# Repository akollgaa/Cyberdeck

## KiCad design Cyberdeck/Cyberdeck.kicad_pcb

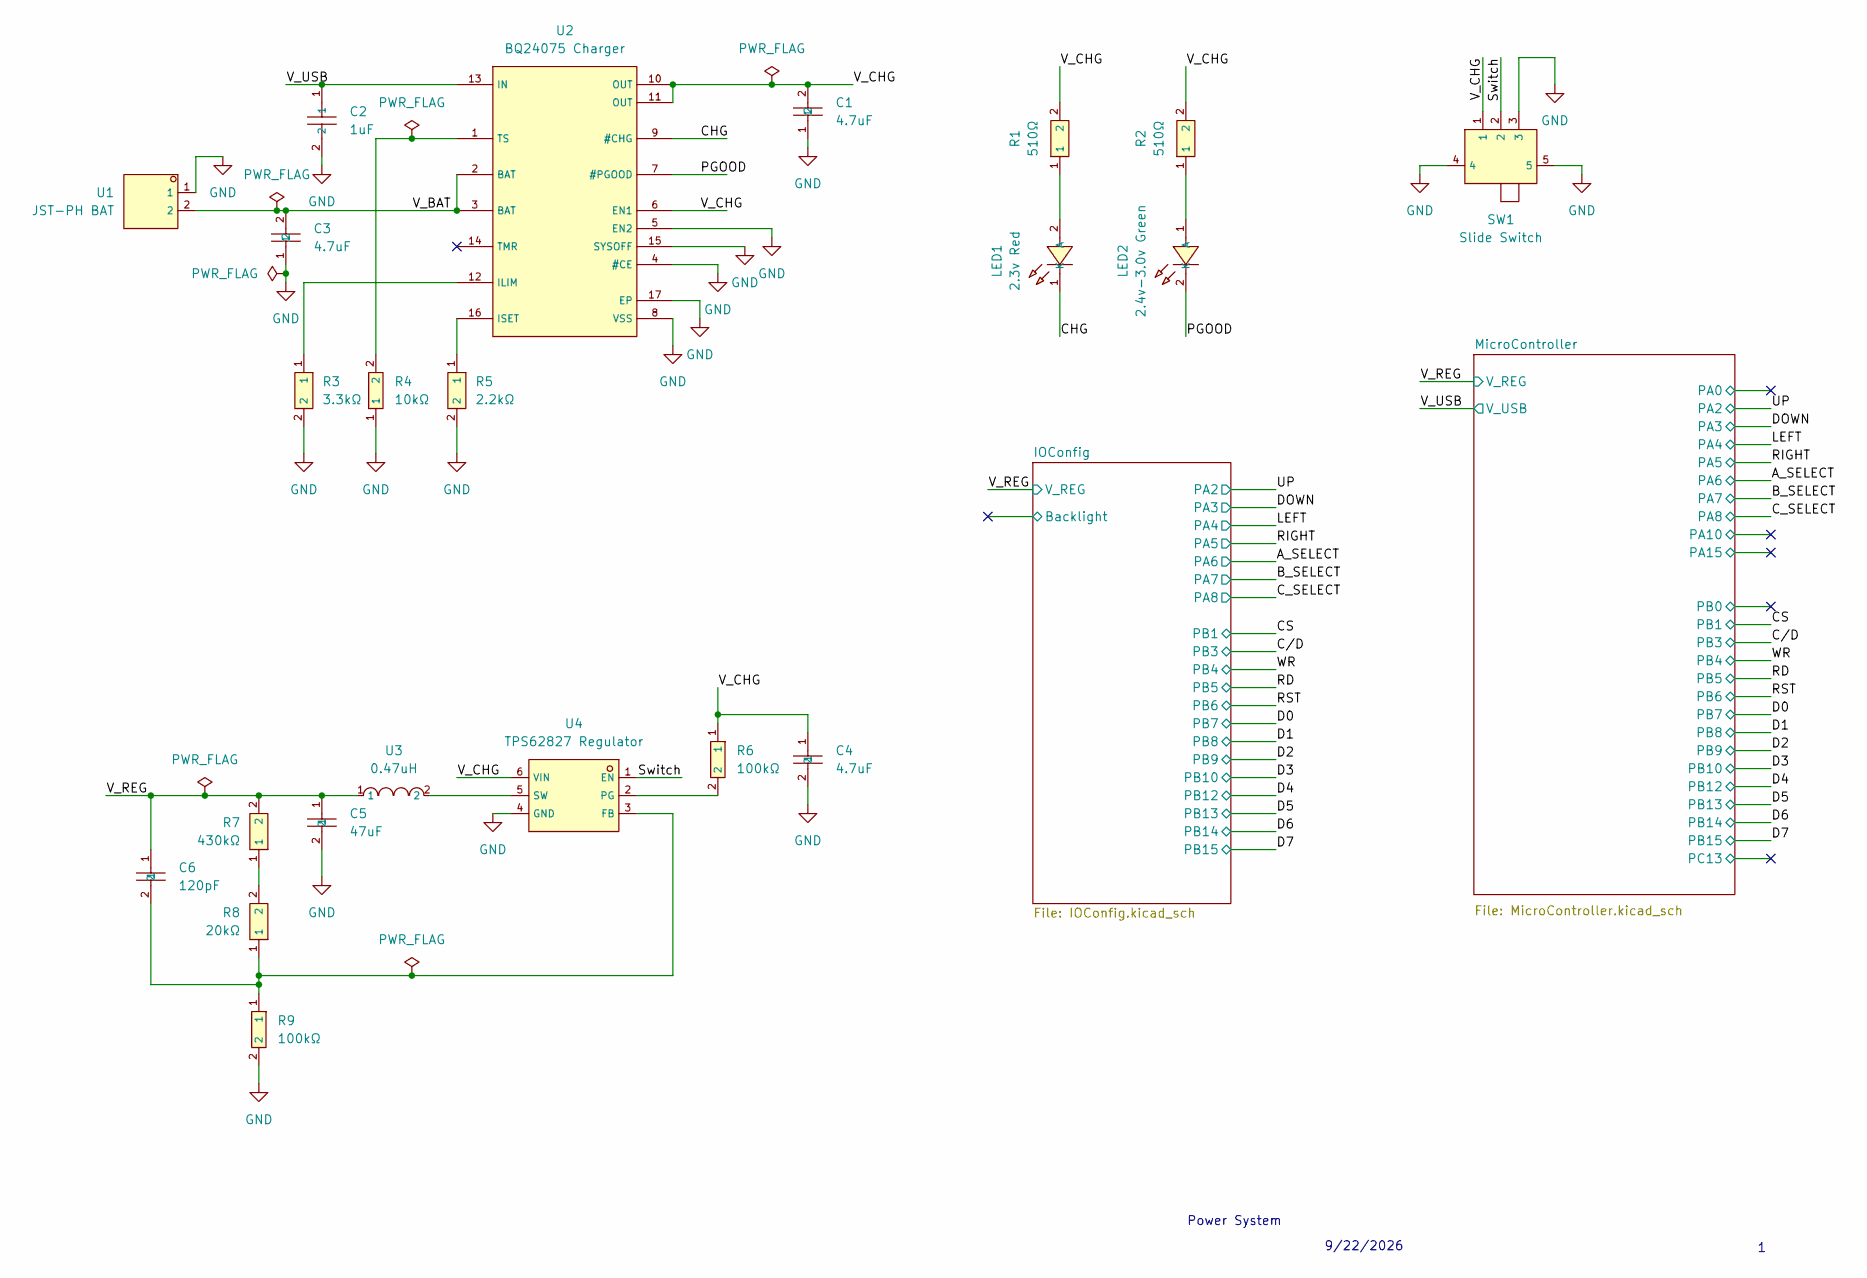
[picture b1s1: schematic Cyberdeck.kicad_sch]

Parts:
C1, C3, C4: 4.7uF; C69335_C0603; LCSC C69335
C2: 1uF; C5199872_C0603; LCSC C5199872
C5: 47uF; C140782_C0603; LCSC C140782
C6: 120pF; C107035_C0603; LCSC C107035
LED1: 2.3v Red; C965799_LED0603-RD_RED; LCSC C965799
LED2: 2.4v-3.0v Green; C19171301_LED0603-FD; LCSC C19171301
R1, R2: 510Ω; C2907048_R0603; LCSC C2907048
R3: 3.3kΩ; C2907023_R0603; LCSC C2907023
R4: 10kΩ; C98220_R0603; LCSC C98220
R5: 2.2kΩ; C2907005_R0603; LCSC C2907005
R6, R9: 100kΩ; C14675_R0603; LCSC C14675
R7: 430kΩ; C2907036_R0603; LCSC C2907036
R8: 20kΩ; C2907011_R0603; LCSC C2907011
SW1: Slide Switch; C2939726_SW-TH_SS12D07VG4; LCSC C2939726
U1: JST-PH BAT; C173752_CONN-TH_S2B-PH-K-S-LF-SN; LCSC C173752
U2: BQ24075 Charger; C15464_QFN-16_L3_0-W3_0-P0_50-TL-EP1_7; LCSC C15464
U3: 0.47uH; C269773_L0806; LCSC C269773
U4: TPS62827 Regulator; C2071448_VSON-6_L1_5-W1_5-P0_50-TL; LCSC C2071448

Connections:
/CHG: LED1.1 (K), U2.9 (#CHG)
/PGOOD: LED2.2 (K), U2.7 (#PGOOD)
/Switch: SW1.2, U4.1 (EN)
/V_BAT: C3.2, U1.2, U2.2 (BAT), U2.3 (BAT)
/V_CHG: C1.2, C4.1, R1.2, R2.2, R6.1, SW1.1, U2.6 (EN1), U2.10 (OUT), U2.11 (OUT), U4.6 (VIN)
/V_REG: C5.1, C6.1, R7.2, U3.1; also elsewhere on the board
/V_USB: C2.1, U2.13 (IN); also elsewhere on the board
GND: C1.1, C2.2, C3.1, C4.2, C5.2, R3.2, R4.1, R5.2, R9.2, SW1.3, SW1.4, SW1.5, U1.1, U2.4 (#CE), U2.5 (EN2), U2.8 (VSS), U2.15 (SYSOFF), U2.17 (EP), U4.4 (GND); also elsewhere on the board
unnamed: LED1.2 (A), R1.1
unnamed: LED2.1 (A), R2.1
unnamed: R7.1, R8.2
unnamed: R3.1, U2.12 (ILIM)
unnamed: R5.1, U2.16 (ISET)
unnamed: R4.2, U2.1 (TS)
unnamed: C6.2, R8.1, R9.1, U4.3 (FB)
unnamed: R6.2, U4.2 (PG)
unnamed: U3.2, U4.5 (SW)

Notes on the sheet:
9/22/2026
Power System

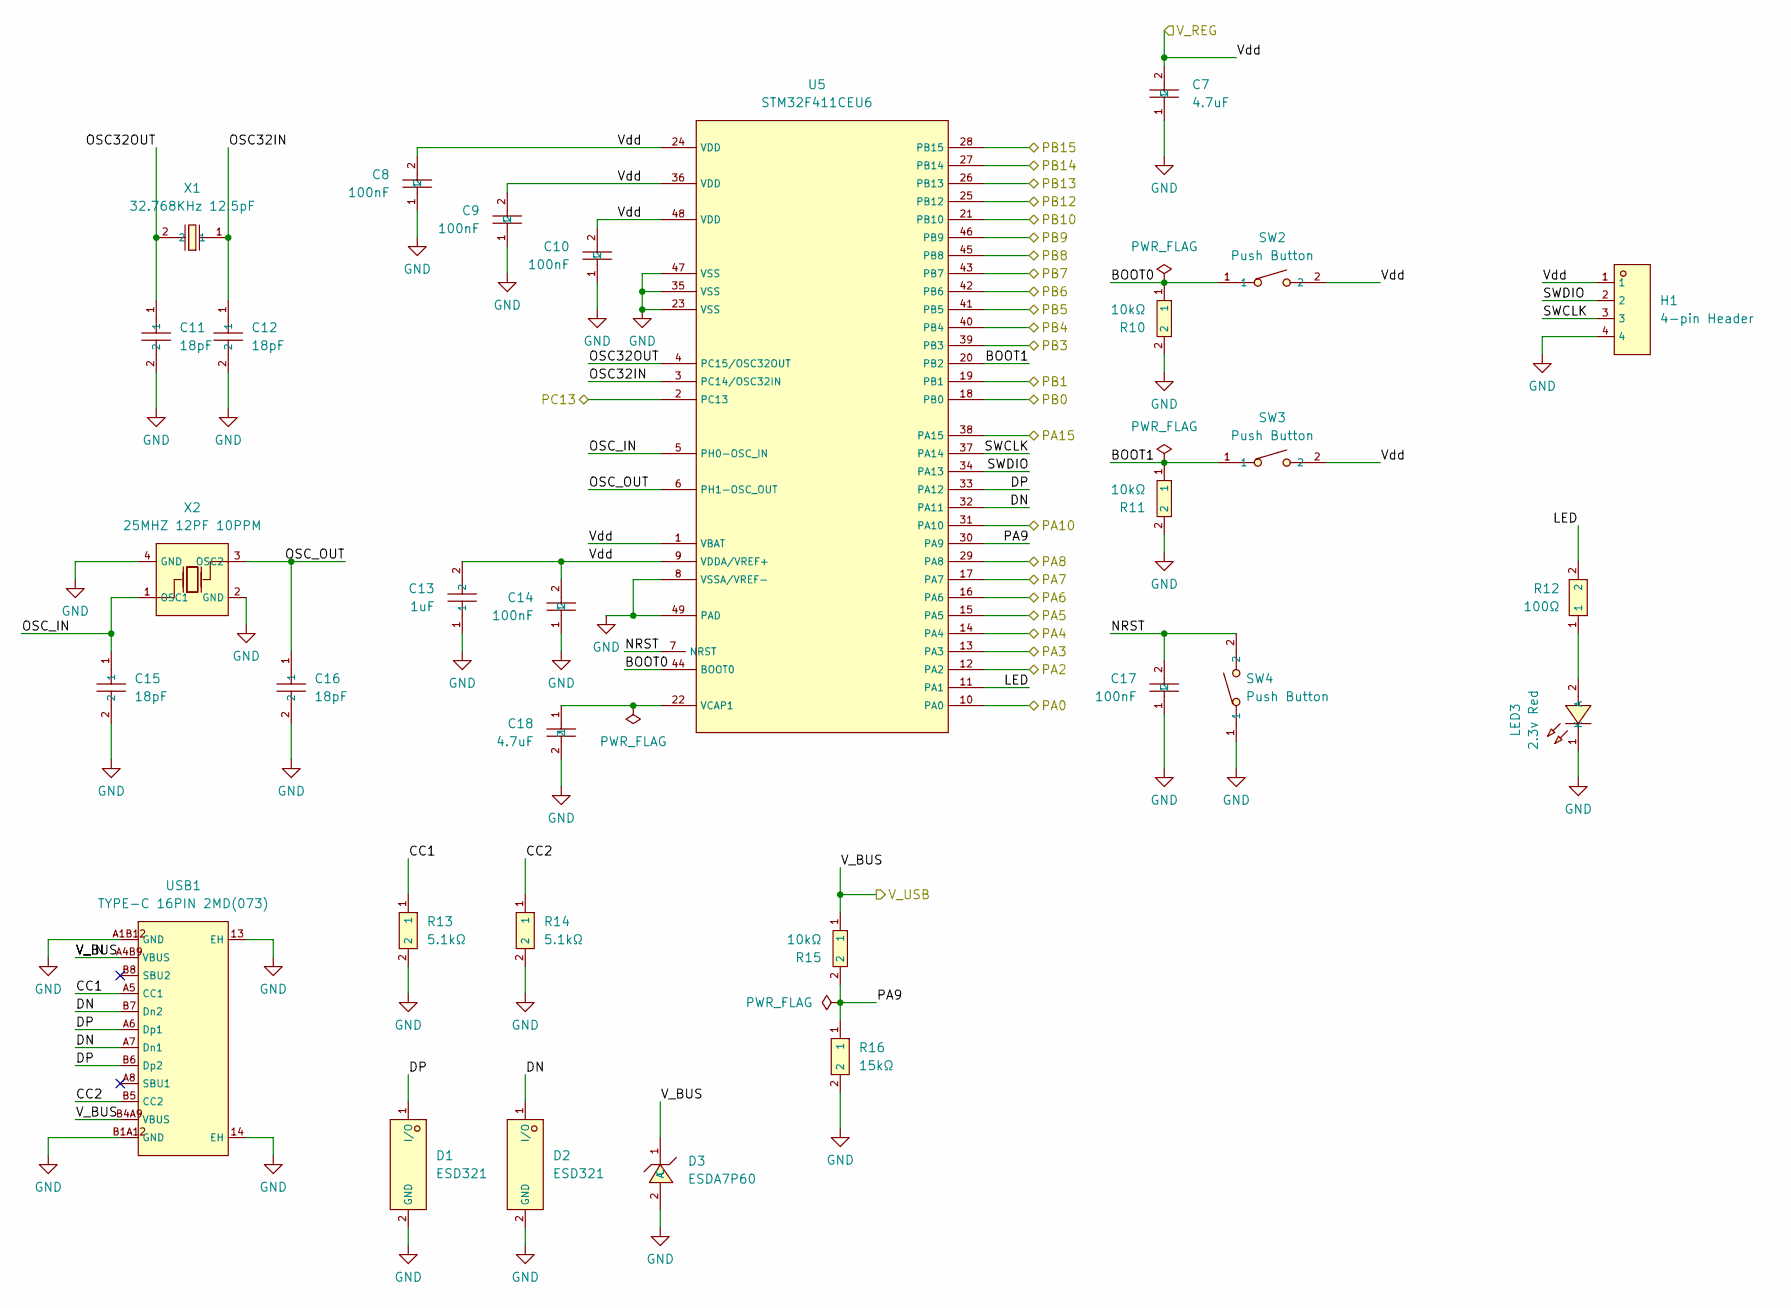
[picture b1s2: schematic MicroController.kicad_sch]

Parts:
C7, C18: 4.7uF; C69335_C0603; LCSC C69335
C8, C9, C10, C14, C17: 100nF; C66501_C0603; LCSC C66501
C11, C12, C15, C16: 18pF; C541431_C0402; LCSC C541431
C13: 1uF; C5199872_C0603; LCSC C5199872
D1, D2: ESD321; C2868952_X1SON-2_L1_0-W0_6-P0_65-RD-1; LCSC C2868952
D3: ESDA7P60; C1975146_D1610-RD; LCSC C1975146
H1: 4-pin Header; C2691448_HDR-TH_4P-P2_54-V-M; LCSC C2691448
LED3: 2.3v Red; C965799_LED0603-RD_RED; LCSC C965799
R10, R11, R15: 10kΩ; C98220_R0603; LCSC C98220
R12: 100Ω; C2906981_R0603; LCSC C2906981
R13, R14: 5.1kΩ; C2907044_R0603; LCSC C2907044
R16: 15kΩ; C2906995_R0603; LCSC C2906995
SW2, SW3, SW4: Push Button; C720477_SW-SMD_L3_9-W3_0-P4_45; LCSC C720477
U5: STM32F411CEU6; C60420_UFQFPN-48_L7_0-W7_0-P0_50-BL-EP; LCSC C60420
USB1: TYPE-C 16PIN 2MD(073); C2765186_USB-C-SMD_TYPE-C-16PIN-2MD-073; LCSC C2765186
X1: 32.768KHz 12.5pF; C32346_FC-135R_L3_2-W1_5; LCSC C32346
X2: 25MHZ 12PF 10PPM; C9006_CRYSTAL-SMD_4P-L3_2-W2_5-BL; LCSC C9006

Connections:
/A_SELECT: U5.16 (PA6); also elsewhere on the board
/B_SELECT: U5.17 (PA7); also elsewhere on the board
/CS: U5.19 (PB1); also elsewhere on the board
/C_SELECT: U5.29 (PA8); also elsewhere on the board
/C/D: U5.39 (PB3); also elsewhere on the board
/D0: U5.43 (PB7); also elsewhere on the board
/D1: U5.45 (PB8); also elsewhere on the board
/D2: U5.46 (PB9); also elsewhere on the board
/D3: U5.21 (PB10); also elsewhere on the board
/D4: U5.25 (PB12); also elsewhere on the board
/D5: U5.26 (PB13); also elsewhere on the board
/D6: U5.27 (PB14); also elsewhere on the board
/D7: U5.28 (PB15); also elsewhere on the board
/DOWN: U5.13 (PA3); also elsewhere on the board
/LEFT: U5.14 (PA4); also elsewhere on the board
/MicroController/BOOT0: R10.1, SW2.1, U5.44 (BOOT0)
/MicroController/BOOT1: R11.1, SW3.1, U5.20 (PB2)
/MicroController/CC1: R13.1, USB1.A5 (CC1)
/MicroController/CC2: R14.1, USB1.B5 (CC2)
/MicroController/DN: D2.1 (I/O), U5.32 (PA11), USB1.A7 (Dn1), USB1.B7 (Dn2)
/MicroController/DP: D1.1 (I/O), U5.33 (PA12), USB1.A6 (Dp1), USB1.B6 (Dp2)
/MicroController/LED: R12.2, U5.11 (PA1)
/MicroController/NRST: C17.2, SW4.2, U5.7 (NRST)
/MicroController/OSC32IN: C12.1, U5.3 (PC14/OSC32IN), X1.1
/MicroController/OSC32OUT: C11.1, U5.4 (PC15/OSC32OUT), X1.2
/MicroController/OSC_IN: C15.1, U5.5 (PH0-OSC_IN), X2.1 (OSC1)
/MicroController/OSC_OUT: C16.1, U5.6 (PH1-OSC_OUT), X2.3 (OSC2)
/MicroController/PA0: U5.10 (PA0); also elsewhere on the board
/MicroController/PA9: R15.2, R16.1, U5.30 (PA9)
/MicroController/PA10: U5.31 (PA10); also elsewhere on the board
/MicroController/PA15: U5.38 (PA15); also elsewhere on the board
/MicroController/PB0: U5.18 (PB0); also elsewhere on the board
/MicroController/PC13: U5.2 (PC13); also elsewhere on the board
/MicroController/SWCLK: H1.3, U5.37 (PA14)
/MicroController/SWDIO: H1.2, U5.34 (PA13)
/RD: U5.41 (PB5); also elsewhere on the board
/RIGHT: U5.15 (PA5); also elsewhere on the board
/RST: U5.42 (PB6); also elsewhere on the board
/UP: U5.12 (PA2); also elsewhere on the board
/V_REG: C7.2, C8.2, C9.2, C10.2, C13.2, C14.2, H1.1, SW2.2, SW3.2, U5.1 (VBAT), U5.9 (VDDA/VREF+), U5.24 (VDD), U5.36 (VDD), U5.48 (VDD); also elsewhere on the board
/V_USB: D3.1 (C), R15.1, USB1.A4B9 (VBUS), USB1.B4A9 (VBUS); also elsewhere on the board
/WR: U5.40 (PB4); also elsewhere on the board
GND: C7.1, C8.1, C9.1, C10.1, C11.2, C12.2, C13.1, C14.1, C15.2, C16.2, C17.1, C18.2, D1.2 (GND), D2.2 (GND), D3.2 (A), H1.4, LED3.1 (K), R10.2, R11.2, R13.2, R14.2, R16.2, SW4.1, U5.8 (VSSA/VREF-), U5.23 (VSS), U5.35 (VSS), U5.47 (VSS), U5.49 (PAD), USB1.13 (EH), USB1.14 (EH), USB1.A1B12 (GND), USB1.B1A12 (GND), X2.2 (GND), X2.4 (GND); also elsewhere on the board
unnamed: LED3.2 (A), R12.1
unnamed: C18.1, U5.22 (VCAP1)

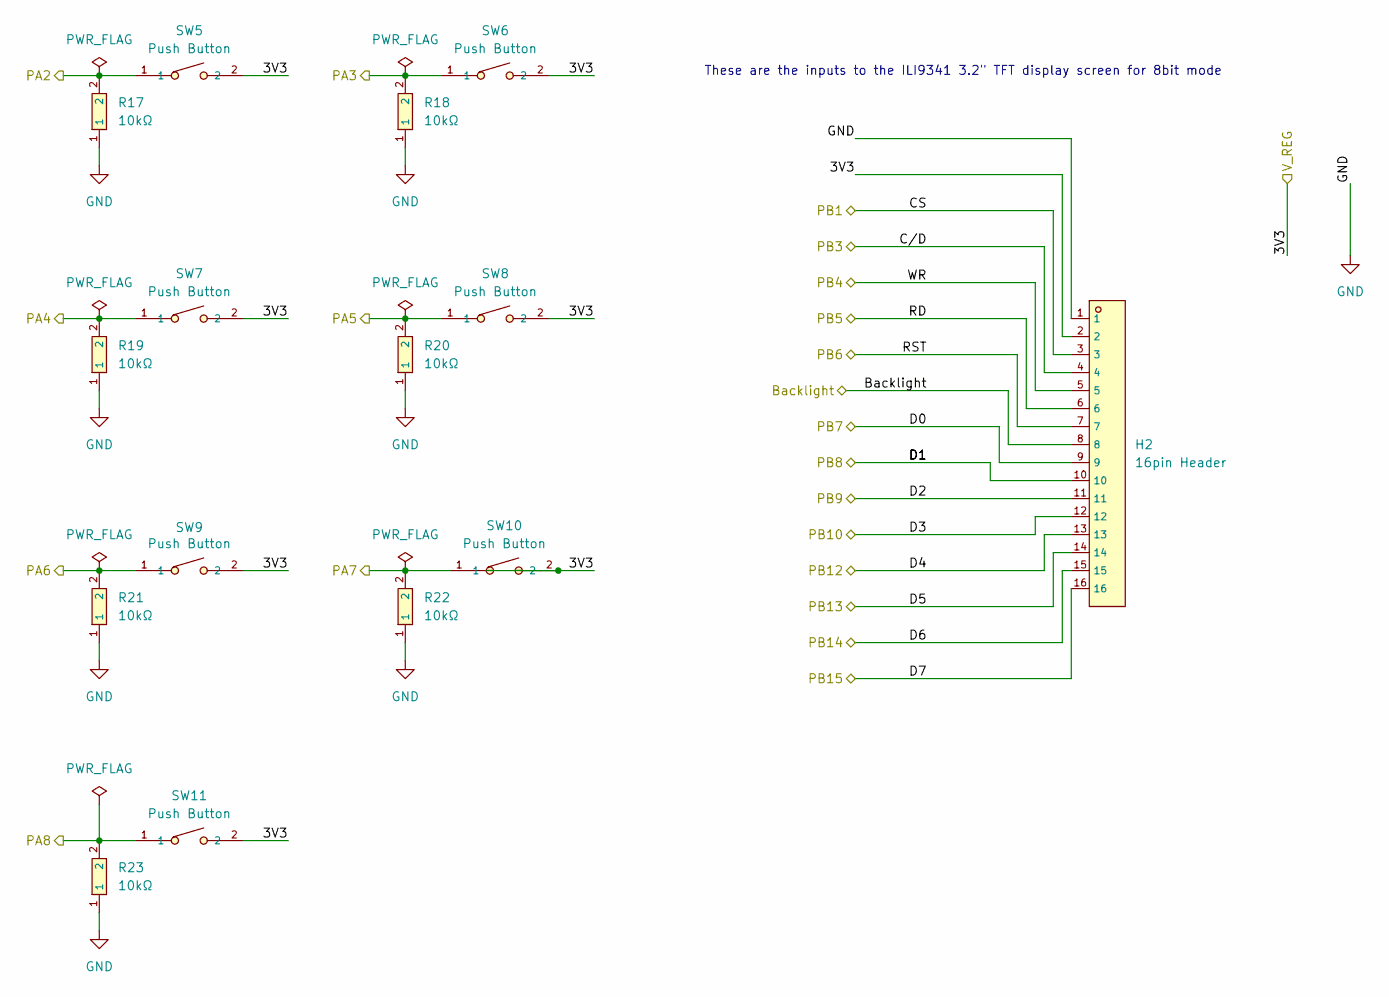
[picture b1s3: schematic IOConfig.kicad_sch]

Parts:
H2: 16pin Header; C2894939_HDR-TH_16P-P2_54-V-M; LCSC C2894939
R17, R18, R19, R20, R21, R22, R23: 10kΩ; C98220_R0603; LCSC C98220
SW5, SW6, SW7, SW8, SW9, SW10, SW11: Push Button; C720477_SW-SMD_L3_9-W3_0-P4_45; LCSC C720477

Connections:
/A_SELECT: R21.2, SW9.1; also elsewhere on the board
/B_SELECT: R22.2, SW10.1; also elsewhere on the board
/CS: H2.3; also elsewhere on the board
/C_SELECT: R23.2, SW11.1; also elsewhere on the board
/C/D: H2.4; also elsewhere on the board
/D0: H2.9; also elsewhere on the board
/D1: H2.10; also elsewhere on the board
/D2: H2.11; also elsewhere on the board
/D3: H2.12; also elsewhere on the board
/D4: H2.13; also elsewhere on the board
/D5: H2.14; also elsewhere on the board
/D6: H2.15; also elsewhere on the board
/D7: H2.16; also elsewhere on the board
/DOWN: R18.2, SW6.1; also elsewhere on the board
/IOConfig/Backlight: H2.8
/LEFT: R19.2, SW7.1; also elsewhere on the board
/RD: H2.6; also elsewhere on the board
/RIGHT: R20.2, SW8.1; also elsewhere on the board
/RST: H2.7; also elsewhere on the board
/UP: R17.2, SW5.1; also elsewhere on the board
/V_REG: H2.2, SW5.2, SW6.2, SW7.2, SW8.2, SW9.2, SW10.2, SW11.2; also elsewhere on the board
/WR: H2.5; also elsewhere on the board
GND: H2.1, R17.1, R18.1, R19.1, R20.1, R21.1, R22.1, R23.1; also elsewhere on the board

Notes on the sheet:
These are the inputs to the ILI9341 3.2" TFT display screen for 8bit mode

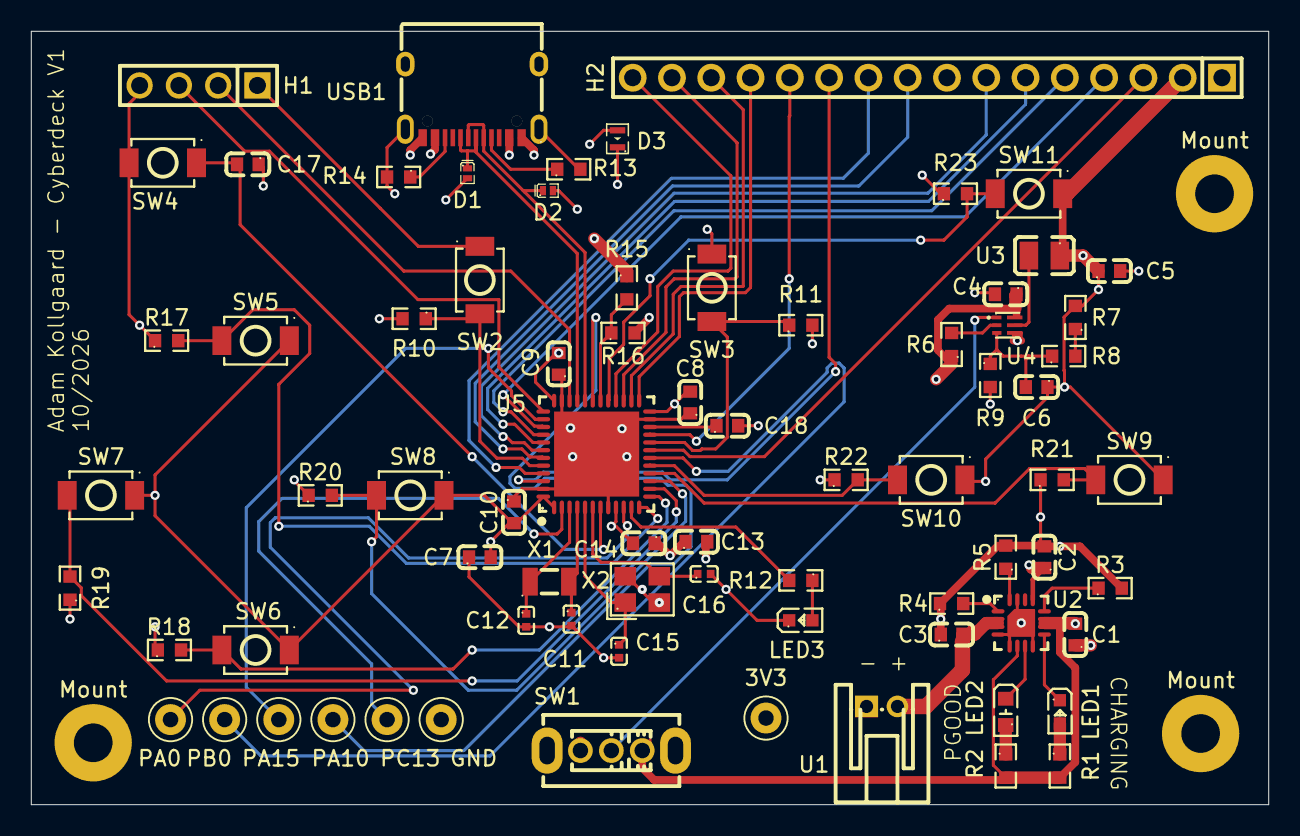
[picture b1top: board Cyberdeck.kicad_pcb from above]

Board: 4 copper layers, 80.0 x 50.0 mm, 78 parts (0 on the bottom side), 59 nets.

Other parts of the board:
3V3: TestPoint; TestPoint_Keystone_5000-5004_Miniature
GND: TestPoint; TestPoint_Keystone_5000-5004_Miniature
Mount: MountingHole; MountingHole_2.5mm_Pad
Mount#2, Mount#3: MountingHole; MountingHole_2.5mm_Pad
PA0, PA10, PA15: TestPoint; TestPoint_Keystone_5000-5004_Miniature
PB0: TestPoint; TestPoint_Keystone_5000-5004_Miniature
PC13: TestPoint; TestPoint_Keystone_5000-5004_Miniature

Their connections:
/MicroController/PA0: PA0.1; also elsewhere on the board
/MicroController/PA10: PA10.1; also elsewhere on the board
/MicroController/PA15: PA15.1; also elsewhere on the board
/MicroController/PB0: PB0.1; also elsewhere on the board
/MicroController/PC13: PC13.1; also elsewhere on the board
/V_REG: 3V3.1; also elsewhere on the board
GND: GND.1, Mount.1, Mount#2.1, Mount#3.1; also elsewhere on the board

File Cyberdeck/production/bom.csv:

Designator,Footprint,Quantity,Value,LCSC Part #
"C1, C18, C3, C4, C7",C69335_C0603,5,4.7uF,C69335
"C10, C14, C17, C8, C9",C66501_C0603,5,100nF,C66501
"C11, C12, C15, C16",C541431_C0402,4,18pF,C541431
"C13, C2",C5199872_C0603,2,1uF,C5199872
C5,C140782_C0603,1,47uF,C140782
C6,C107035_C0603,1,120pF,C107035
"D1, D2",C2868952_X1SON-2_L1_0-W0_6-P0_65-RD-1,2,ESD321,C2868952
D3,C1975146_D1610-RD,1,ESDA7P60,C1975146
H1,C2691448_HDR-TH_4P-P2_54-V-M,1,4-pin Header,C2691448
H2,C2894939_HDR-TH_16P-P2_54-V-M,1,16pin Header,C2894939
"LED1, LED3",C965799_LED0603-RD_RED,2,2.3v Red,C965799
LED2,C19171301_LED0603-FD,1,2.4v-3.0v Green,C19171301
"R1, R2",C2907048_R0603,2,510Ω,C2907048
"R10, R11, R15, R17, R18, R19, R20, R21, R22, R23, R4",C98220_R0603,11,10kΩ,C98220
R12,C2906981_R0603,1,100Ω,C2906981
"R13, R14",C2907044_R0603,2,5.1kΩ,C2907044
R16,C2906995_R0603,1,15kΩ,C2906995
R3,C2907023_R0603,1,3.3kΩ,C2907023
R5,C2907005_R0603,1,2.2kΩ,C2907005
"R6, R9",C14675_R0603,2,100kΩ,C14675
R7,C2907036_R0603,1,430kΩ,C2907036
R8,C2907011_R0603,1,20kΩ,C2907011
SW1,C2939726_SW-TH_SS12D07VG4,1,Slide Switch,C2939726
"SW10, SW11, SW2, SW3, SW4, SW5, SW6, SW7, SW8, SW9",C720477_SW-SMD_L3_9-W3_0-P4_45,10,Push Button,C720477
U1,C173752_CONN-TH_S2B-PH-K-S-LF-SN,1,JST-PH BAT,C173752
U2,C15464_QFN-16_L3_0-W3_0-P0_50-TL-EP1_7,1,BQ24075 Charger,C15464
U3,C269773_L0806,1,0.47uH,C269773
U4,C2071448_VSON-6_L1_5-W1_5-P0_50-TL,1,TPS62827 Regulator,C2071448
U5,C60420_UFQFPN-48_L7_0-W7_0-P0_50-BL-EP,1,STM32F411CEU6,C60420
USB1,C2765186_USB-C-SMD_TYPE-C-16PIN-2MD-073,1,TYPE-C 16PIN 2MD(073),C2765186
X1,C32346_FC-135R_L3_2-W1_5,1,32.768KHz 12.5pF,C32346
X2,C9006_CRYSTAL-SMD_4P-L3_2-W2_5-BL,1,25MHZ 12PF 10PPM,C9006

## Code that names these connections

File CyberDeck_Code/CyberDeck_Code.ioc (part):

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Mcu.Name=STM32F411C(C-E)Ux
Mcu.Package=UFQFPN48
Mcu.UserName=STM32F411CEUx
PA1.Signal=GPIO_Output
PA11.Mode=Device_Only
PA11.Signal=USB_OTG_FS_DM
PA12.Mode=Device_Only
PA12.Signal=USB_OTG_FS_DP
PA13.Mode=Serial_Wire
PA13.Signal=SYS_JTMS-SWDIO
PA14.Mode=Serial_Wire
PA14.Signal=SYS_JTCK-SWCLK
PA2.Signal=GPIO_Input
PA3.Signal=GPIO_Input
PA4.Signal=GPIO_Input
PA5.Signal=GPIO_Input
PA6.Signal=GPIO_Input
PA7.Signal=GPIO_Input
PA8.Signal=GPIO_Input
PA9.Mode=Activate_VBUS
PA9.Signal=USB_OTG_FS_VBUS
PB1.GPIOParameters=GPIO_Speed
PB1.GPIO_Speed=GPIO_SPEED_FREQ_VERY_HIGH
PB1.Signal=GPIO_Output
PB10.GPIOParameters=GPIO_Speed
PB10.GPIO_Speed=GPIO_SPEED_FREQ_VERY_HIGH
PB10.Signal=GPIO_Output
PB12.GPIOParameters=GPIO_Speed
PB12.GPIO_Speed=GPIO_SPEED_FREQ_VERY_HIGH
PB12.Signal=GPIO_Output
PB13.GPIOParameters=GPIO_Speed
PB13.GPIO_Speed=GPIO_SPEED_FREQ_VERY_HIGH
PB13.Signal=GPIO_Output
PB14.GPIOParameters=GPIO_Speed
PB14.GPIO_Speed=GPIO_SPEED_FREQ_VERY_HIGH
PB14.Signal=GPIO_Output
PB15.GPIOParameters=GPIO_Speed
PB15.GPIO_Speed=GPIO_SPEED_FREQ_VERY_HIGH
PB15.Signal=GPIO_Output
PB3.GPIOParameters=GPIO_Speed
PB3.GPIO_Speed=GPIO_SPEED_FREQ_VERY_HIGH
PB3.Signal=GPIO_Output
PB4.GPIOParameters=GPIO_Speed
PB4.GPIO_Speed=GPIO_SPEED_FREQ_VERY_HIGH
PB4.Signal=GPIO_Output
PB5.GPIOParameters=GPIO_Speed
PB5.GPIO_Speed=GPIO_SPEED_FREQ_VERY_HIGH
PB5.Signal=GPIO_Output
PB6.GPIOParameters=GPIO_Speed
PB6.GPIO_Speed=GPIO_SPEED_FREQ_VERY_HIGH
PB6.Signal=GPIO_Output
PB7.GPIOParameters=GPIO_Speed
PB7.GPIO_Speed=GPIO_SPEED_FREQ_VERY_HIGH
PB7.Signal=GPIO_Output
PB8.GPIOParameters=GPIO_Speed
PB8.GPIO_Speed=GPIO_SPEED_FREQ_VERY_HIGH
PB8.Signal=GPIO_Output
PB9.GPIOParameters=GPIO_Speed
PB9.GPIO_Speed=GPIO_SPEED_FREQ_VERY_HIGH
PB9.Signal=GPIO_Output
PC14-OSC32_IN.Mode=LSE-External-Oscillator
PC14-OSC32_IN.Signal=RCC_OSC32_IN
PC15-OSC32_OUT.Mode=LSE-External-Oscillator
PC15-OSC32_OUT.Signal=RCC_OSC32_OUT
PH0\ -\ OSC_IN.Mode=HSE-External-Oscillator
PH0\ -\ OSC_IN.Signal=RCC_OSC_IN
PH1\ -\ OSC_OUT.Mode=HSE-External-Oscillator
PH1\ -\ OSC_OUT.Signal=RCC_OSC_OUT
RCC.HSE_VALUE=25000000
RCC.SYSCLKFreq_VALUE=96000000
RCC.SYSCLKSource=RCC_SYSCLKSOURCE_PLLCLK
board=custom
